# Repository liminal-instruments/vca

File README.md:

# Discrete Blackmer VCA

An open, low-cost voltage-controlled amplifier built from discrete matched transistor pairs, intended
as a replacement for the THAT 2180/2181 after THAT Corporation's September 2026 end-of-life notice.

**Status: simulation and schematic only. No hardware has been built or measured yet.**

## Goals

- A modern Blackmer log/antilog gain cell from cheap, available parts (Nexperia BCM847DS / BCM857DS
  matched pairs and one dual op-amp), not an at-any-cost replica.
- Parts cost comparable to a CoolAudio V2181: currently about **£2.01 per module at 100-off**
  (see `bom/bom_v0.csv`; passives are estimates).
- THD below 0.01 % after trimming. The circuit works untrimmed; calibration improves it.

## The circuit

The 8-transistor gain cell described by Hebert (AES preprint 4055, Fig. 4): a log/antilog quad with
two cross-coupled correction pairs, an op-amp input amplifier, a bias generator built from the same
matched pairs. Three trimmers set symmetry, slope symmetry and unity gain. Control law is about
5.9 mV/dB.

The hardware is a module with the THAT 2181's SIP-8 pinout and pin pitch: current in, current out,
with the input resistor and current-to-voltage converter on the host board, as for a 2181. One
difference: the module's op-amp needs the real negative rail, which a 2181 socket does not carry
(pin 5 is a current-programming pin), so -15 V comes in on a separate pad.

Schematic: [`hardware/blackmer_vca/blackmer_vca.pdf`](hardware/blackmer_vca/blackmer_vca.pdf).
The PCB (`blackmer_vca.kicad_pcb`, 56 x 38 mm, two layers) has a script-generated first-pass routing
that passes KiCad's design-rule check but has not been reviewed or optimised by hand.

## Simulated performance

ngspice, vendor transistor and OPA1678 models, pairs at datasheet-limit mismatch, 1 kHz, after trim.
The other columns are manufacturers' datasheet figures for comparison, not simulations.

| Gain | Input | This design (simulated) | THAT 2181 A / B / C (typ) | THAT 2181 A / B / C (max) | CoolAudio V2181 |
|---|---|---|---|---|---|
| -30 dB | 3.16 Vrms | 0.0015 % | - | - | - |
| -15 dB | 3.16 Vrms | 0.0024 % | 0.018 / 0.025 / 0.035 % | 0.025 / 0.035 / 0.07 % | - |
| 0 dB | 1 Vrms | 0.0027 % | 0.0025 / 0.004 / 0.005 % | 0.005 / 0.008 / 0.02 % | 0.008 % |
| 0 dB | 3.16 Vrms | 0.0085 % | 0.004 / 0.006 / 0.015 % | 0.008 / 0.010 / - % | - |
| +15 dB | 0.56 Vrms | 0.010 % | 0.018 / 0.025 / 0.035 % | 0.025 / 0.035 / 0.07 % | 0.035 % |
| +30 dB | 0.1 Vrms | 0.011 % | - | - | - |

- THAT 2181 figures are from the 2181-series datasheet (document 600030 rev 03), at 1 kHz with the
  symmetry trimmed at 1 V, 0 dB. They are measured silicon at 25 C, so they are a far stronger claim
  than the simulation in the first column.
- The CoolAudio V2181 datasheet gives only two headline figures ("0.008 % @ 0 dB gain, 0.035 % @
  15 dB gain") without stating input level or grade; they are placed on the nearest rows.
- Noise has not been simulated yet, so no noise comparison is given.

Untrimmed, the same worst-case parts give 0.04-0.18 %. Known limits and open work:

- Distortion rises with frequency (about 0.026 % at 10 kHz untrimmed) because of the input-amplifier
  compensation capacitor.
- The vendor transistor models have no temperature dependence, so trim drift is not yet characterised.
- Noise, Monte Carlo and temperature sweeps have not been run.
- Results are from ngspice only; they have not been cross-checked in LTspice or on a bench.

## Repository layout

| Path | Contents |
|---|---|
| `sim/` | ngspice netlists (`lib/`), Python harness and studies, results |
| `hardware/` | KiCad 9 project, schematic generator and netlist check |
| `bom/` | Bill of materials with 100-off prices |
| `docs/` | Patents, and links to the papers and datasheets used |
| `models/` | Where to put the vendor SPICE models (not redistributed here) |

## Running the simulations

Requires ngspice (45 or later) and Python 3.

```
python3 -m venv .venv && .venv/bin/pip install -r requirements.txt
# download the vendor models listed in models/README.md
cd sim
../.venv/bin/python study_cells.py           # 4- vs 8-transistor cell, ideal vs real devices
../.venv/bin/python study_trim.py OPA1678    # three-trimmer calibration
../.venv/bin/python study_comp.py OPA1678    # input-amplifier compensation sweep
```

## Regenerating the schematic

Requires KiCad 9 with its standard symbol libraries.

```
cd hardware
python3 gen_schematic.py     # writes blackmer_vca/blackmer_vca.kicad_sch
python3 check_netlist.py     # compares the schematic's netlist with the simulated circuit
python3 gen_board.py         # starting-point PCB (overwrites the board - only before hand edits)
python3 route_board.py       # first-pass routing and ground-pour cut-outs
```

## Disclaimer

This project is not affiliated with or endorsed by THAT Corporation, CoolAudio or any other
manufacturer. Product names are trademarks of their owners and are used only to identify the parts
discussed. The original Blackmer patents have expired.

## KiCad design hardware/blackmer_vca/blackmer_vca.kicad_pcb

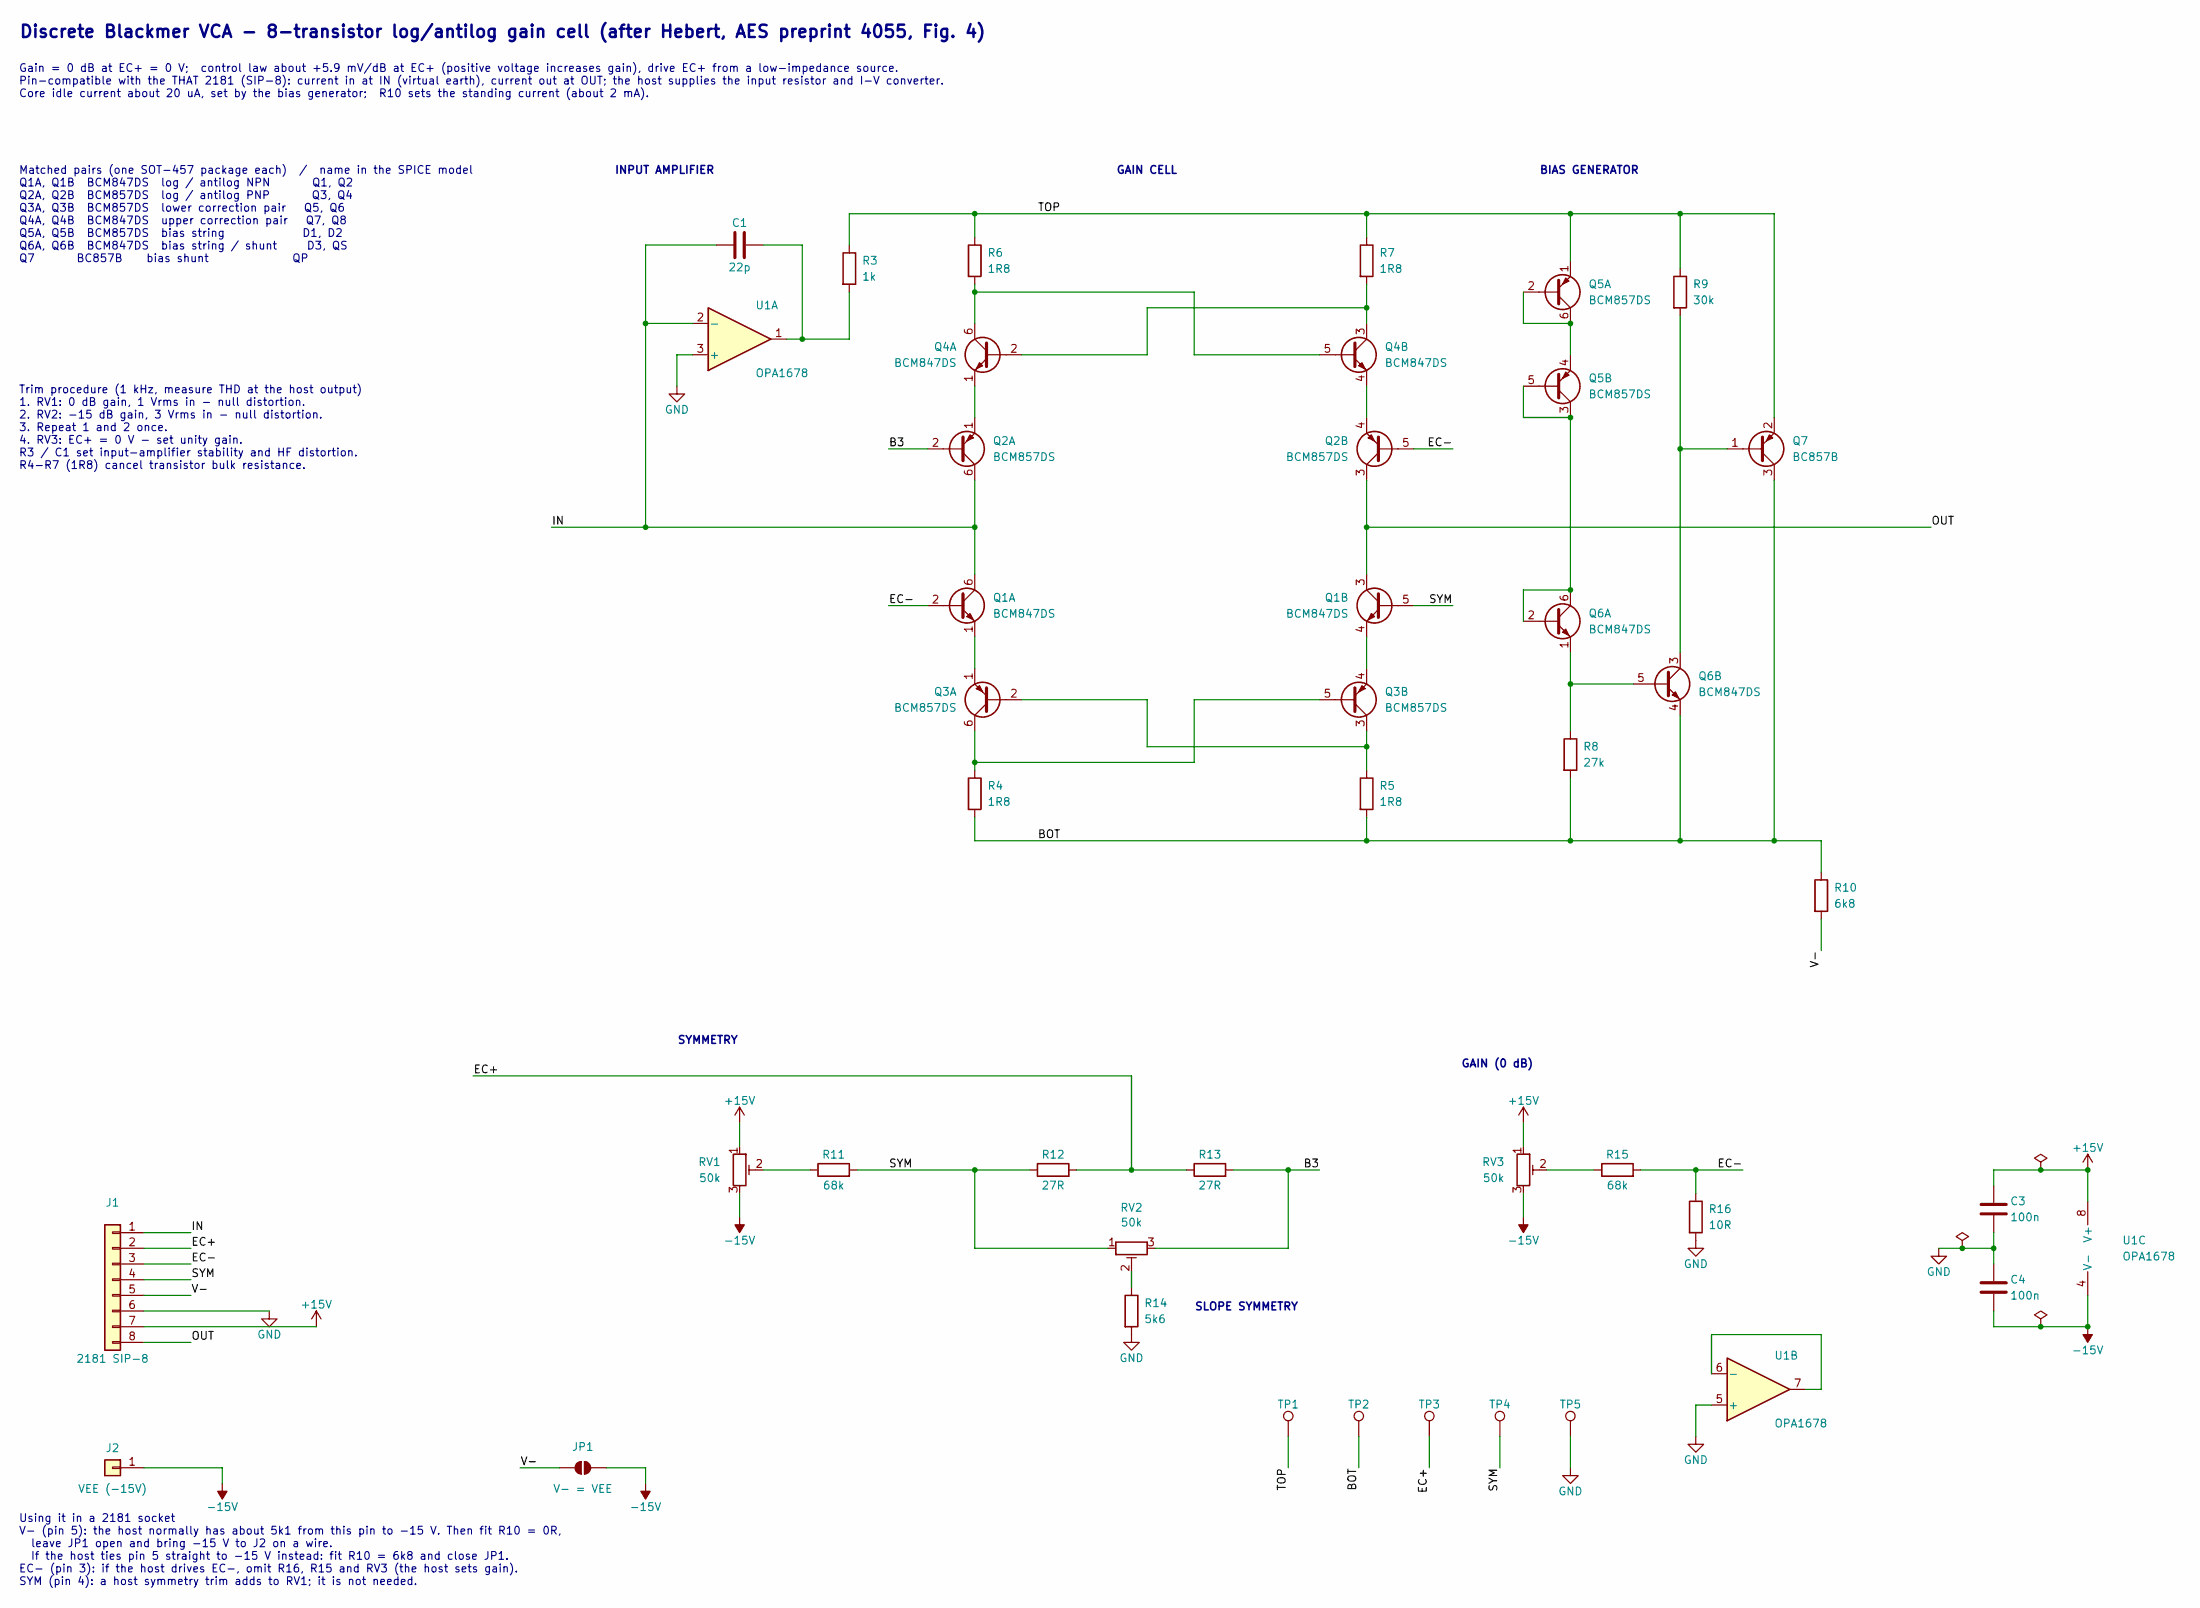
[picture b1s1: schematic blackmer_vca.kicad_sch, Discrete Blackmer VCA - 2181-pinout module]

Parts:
C1: 22p; C_0603_1608Metric
C3, C4: 100n; C_0603_1608Metric
J1: 2181 SIP-8; PinHeader_1x08_P2.54mm_Vertical
J2: VEE (-15V); PinHeader_1x01_P2.54mm_Vertical
JP1: V- = VEE; SolderJumper-2_P1.3mm_Open_RoundedPad1.0x1.5mm
Q1, Q4, Q6: BCM847DS; SC-74-6_1.55x2.9mm_P0.95mm
Q2, Q3, Q5: BCM857DS; SC-74-6_1.55x2.9mm_P0.95mm
Q7: BC857B; SOT-23
R3: 1k; R_0603_1608Metric
R4, R5, R6, R7: 1R8; R_0603_1608Metric
R8: 27k; R_0603_1608Metric
R9: 30k; R_0603_1608Metric
R10: 6k8; R_0603_1608Metric
R11, R15: 68k; R_0603_1608Metric
R12, R13: 27R; R_0603_1608Metric
R14: 5k6; R_0603_1608Metric
R16: 10R; R_0603_1608Metric
RV1, RV2, RV3: 50k; Potentiometer_Bourns_TC33X_Vertical
TP1: TOP; TestPoint_Pad_D1.5mm
TP2: BOT; TestPoint_Pad_D1.5mm
TP3: EC+; TestPoint_Pad_D1.5mm
TP4: SYM; TestPoint_Pad_D1.5mm
TP5: GND; TestPoint_Pad_D1.5mm
U1: OPA1678; SOIC-8_3.9x4.9mm_P1.27mm

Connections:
+15V: C3.1, J1.7, RV1.1, RV3.1, U1.8 (V+)
-15V: C4.2, J2.1, JP1.2 (B), RV1.3, RV3.3, U1.4 (V-)
/B3: Q2.2 (B1), R13.2, RV2.3
/BOT: Q6.4 (E2), Q7.3 (C), R4.2, R5.2, R8.2, R10.1, TP2.1
/EC+: J1.2, R12.2, R13.1, TP3.1
/EC-: J1.3, Q1.2 (B1), Q2.5 (B2), R15.2, R16.1
/IN: C1.1, J1.1, Q1.6 (C1), Q2.6 (C1), U1.2 (-)
/OUT: J1.8, Q1.3 (C2), Q2.3 (C2)
/SYM: J1.4, Q1.5 (B2), R11.2, R12.1, RV2.1, TP4.1
/TOP: Q5.1 (E1), Q7.2 (E), R3.1, R6.1, R7.1, R9.1, TP1.1
/V-: J1.5, JP1.1 (A), R10.2
GND: C3.2, C4.1, J1.6, R14.2, R16.2, TP5.1, U1.3 (+), U1.5 (+)
unnamed: C1.2, R3.2, U1.1
unnamed: Q1.1 (E1), Q3.1 (E1)
unnamed: Q1.4 (E2), Q3.4 (E2)
unnamed: Q2.1 (E1), Q4.1 (E1)
unnamed: Q2.4 (E2), Q4.4 (E2)
unnamed: Q3.2 (B1), Q3.3 (C2), R5.1
unnamed: Q3.5 (B2), Q3.6 (C1), R4.1
unnamed: Q4.2 (B1), Q4.3 (C2), R7.2
unnamed: Q4.5 (B2), Q4.6 (C1), R6.2
unnamed: Q5.2 (B1), Q5.4 (E2), Q5.6 (C1)
unnamed: Q5.3 (C2), Q5.5 (B2), Q6.2 (B1), Q6.6 (C1)
unnamed: Q6.1 (E1), Q6.5 (B2), R8.1
unnamed: Q6.3 (C2), Q7.1 (B), R9.2
unnamed: R11.1, RV1.2
unnamed: R14.1, RV2.2
unnamed: R15.1, RV3.2
unnamed: U1.6 (-), U1.7

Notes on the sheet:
SYMMETRY
SLOPE SYMMETRY
GAIN (0 dB)
Discrete Blackmer VCA - 8-transistor log/antilog gain cell (after Hebert, AES preprint 4055, Fig. 4)
Gain = 0 dB at EC+ = 0 V; control law about +5.9 mV/dB at EC+ (positive voltage increases gain), drive EC+ from a low-impedance source. Pin-compatible with the THAT 2181 (SIP-8): current in at IN (virtual earth), current out at OUT; the host supplies the input resistor and I-V converter. Core idle 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
INPUT AMPLIFIER
GAIN CELL
BIAS GENERATOR
Matched pairs (one SOT-457 package each) / name in the SPICE model Q1A, Q1B BCM847DS log / antilog NPN Q1, Q2 Q2A, Q2B BCM857DS log / antilog PNP Q3, Q4 Q3A, Q3B BCM857DS lower correction pair Q5, Q6 Q4A, Q4B BCM847DS upper correction pair Q7, Q8 Q5A, Q5B BCM857DS bias string D1, D2 Q6A, Q6B BCM847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
Trim procedure (1 kHz, measure THD at the host output) 1. RV1: 0 dB gain, 1 Vrms in - null distortion. 2. RV2: -15 dB gain, 3 Vrms in - null distortion. 3. Repeat 1 and 2 once. 4. RV3: EC+ = 0 V - set unity gain. R3 / C1 set input-amplifier stability and HF distortion. R4-R7 (1R8) cancel transistor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
Using it in a 2181 socket V- (pin 5): the host normally has about 5k1 from this pin to -15 V. Then fit R10 = 0R, leave JP1 open and bring -15 V to J2 on a wire. If the host ties pin 5 straight to -15 V instead: fit R10 = 6k8 and close JP1. EC- (pin 3): if the host drives EC-, omit R16, R15 and RV3 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

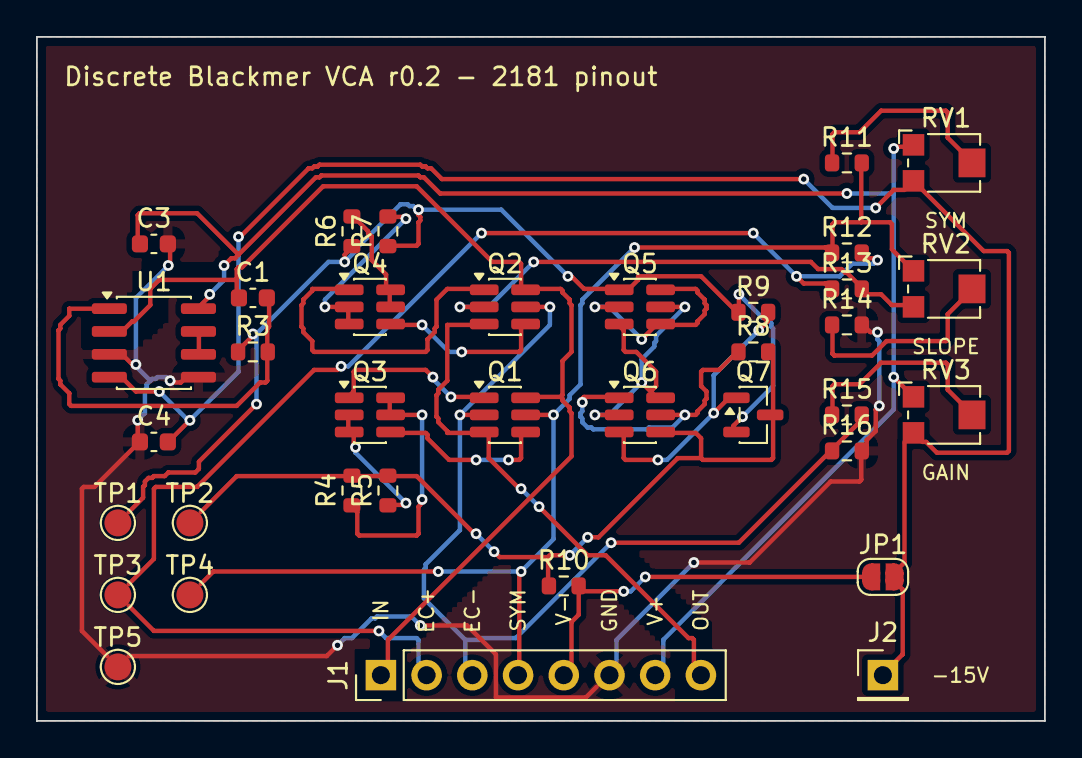
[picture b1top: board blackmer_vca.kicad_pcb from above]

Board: 2 copper layers, 56.0 x 38.0 mm, 36 parts (0 on the bottom side), 29 nets.

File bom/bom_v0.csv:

ref,part,description,qty,unit_gbp_at_100,line_gbp,price_basis
"Q1,Q4,Q6",BCM847DS,"matched NPN pair SOT-457 (log/antilog, upper correction, bias)",3,0.150,0.450,DigiKey UK quote
"Q2,Q3,Q5",BCM857DS,"matched PNP pair SOT-457 (log/antilog, lower correction, bias)",3,0.179,0.537,DigiKey UK quote
Q7,BC857B,PNP SOT-23 (bias shunt),1,0.020,0.020,estimate
U1,OPA1678IDR,dual audio op-amp (input amplifier; second half unused on the module),1,0.350,0.350,DigiKey quote (USD 0.445)
"RV1,RV2,RV3",Bourns TC33X-2-503E,"50k SMD trimmer (symmetry, slope symmetry, gain)",3,0.176,0.528,RS UK quote
"R4,R5,R6,R7",1.8R 1% 0603,correction resistors,4,0.010,0.040,estimate
"R3,R8,R9,R10,R11,R12,R13,R14,R15,R16",1% 0603,"1k,27k,30k,6.8k (or 0R),68k,27R,27R,5.6k,68k,10R",10,0.005,0.050,estimate
C1,22p C0G 0603,compensation,1,0.015,0.015,estimate
"C3,C4",100n X7R 0603,supply decoupling,2,0.010,0.020,estimate
TOTAL per module,,,28,,2.010,
J1,2.54 mm 1x8 pin header,SIP pins,1,0.100,0.100,estimate
"host board",,"input resistor 20k, I-V converter (op-amp half, 20k, 22p) - same as a 2181 needs",,,,

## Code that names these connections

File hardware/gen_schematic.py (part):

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s.wire((96, MID), (XL, MID)); s.label("IN", (96, MID))            # host supplies the input resistor

# ---- rails
s.wire((134, TOP), (252, TOP)); s.label("TOP", (158, TOP))
s.wire((XL, BOT), (258, BOT)); s.label("BOT", (158, BOT))

# ---- bias generator (floating shunt regulator between TOP and BOT)
XS, XQ, XP = 226, 240, 252
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s.wire((XQ, 70), qp["B"])
s.wire((XP, TOP), qp["E"]); s.wire(qp["C"], (XP, BOT))
a, b = s.r("R10", "6k8", 258, 127)                                # RSINK
s.wire((258, BOT), a); s.wire(b, (258, 134)); s.label("V-", (258, 134), 270, "right bottom")

# ---- output: a current, into the host's current-to-voltage converter (as with a 2181)
s.wire((XR, MID), (272, MID)); s.label("OUT", (272, MID))
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s.wire(rv1["2"], ra)
r1a, r1b = s.r("R12", "27R", 160, YT, horiz=True)                 # sim R1
r3a, r3b = s.r("R13", "27R", 180, YT, horiz=True)                 # sim R3
s.wire(rb, r1a); s.label("SYM", (139, YT))
s.wire(r1b, r3a)
s.wire((170, YT), (170, YT - 12), (86, YT - 12)); s.label("EC+", (86, YT - 12))
s.wire(r3b, (194, YT)); s.label("B3", (194, YT), 0, "right bottom")
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       "  leave JP1 open and bring -15 V to J2 on a wire.\n"
       "  If the host ties pin 5 straight to -15 V instead: fit R10 = 6k8 and close JP1.\n"
       "EC- (pin 3): if the host drives EC-, omit R16, R15 and RV3 (the host sets gain).\n"
       "SYM (pin 4): a host symmetry trim adds to RV1; it is not needed.",
       28, 206)

s.write("Discrete Blackmer VCA - 2181-pinout module", "0.2")
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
